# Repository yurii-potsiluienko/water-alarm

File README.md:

# Water Alarm

## Overview

This project was created to learn the fundamentals of PCB design using KiCad, develop mechanical CAD skills in FreeCAD by designing a 3D-printed enclosure, and build a practical, functional device.

The project was inspired by the [KiCad course by DigiKey on YouTube](https://www.youtube.com/watch?v=0WCi1rhueH4&list=PLEBQazB0HUyQ5YJSdCBb79orXaR3Uk5vm), with some modifications to the original circuit.

## Components

- [Buzzer](https://www.digikey.ca/en/products/detail/pui-audio-inc/AI-3035-TT-12V-R/9083403)
- [MOSFET](https://www.digikey.ca/en/products/detail/diotec-semiconductor/2N7000/13164314)
- [Screw terminal](https://www.digikey.ca/en/products/detail/adam-tech/EBAA-02-C/13586872)
- [LED](https://www.digikey.ca/en/products/detail/liteon/LTL-4234/200373)
- [10 MΩ resistor](https://www.digikey.ca/en/products/detail/stackpole-electronics-inc/CF18JT10M0/1741568)
- [6.8 kΩ resistor](https://www.digikey.ca/en/products/detail/stackpole-electronics-inc/CF18JT6K80/1741748)
- [1 nF capacitor](https://www.digikey.ca/en/products/detail/vishay-beyschlag-draloric-bc-components/K102K10X7RH5UL2/2820341)
- [Tactile switch](https://www.digikey.ca/en/products/detail/te-connectivity-alcoswitch-switches/1825910-6/1632536)
- [9 V battery](https://www.digikey.ca/en/products/detail/panasonic-energy/6LF22XWA-B/5067196)
- [Heat-set inserts](https://www.digikey.ca/en/products/detail/adafruit-industries-llc/4255/10244656)
- [M3 screws](https://www.digikey.ca/en/products/detail/w%C3%BCrth-elektronik/97790603111/10056387)

## Tools Used

- KiCad (schematic capture and PCB layout)
- FreeCAD (enclosure design)
- GitHub (version control and documentation)

## What I Learned

- Creating schematics in KiCad
- PCB component placement
- Trace routing and board layout
- Designing and 3D-printing an enclosure to fit a custom PCB

## Images

### Schematic

### PCB Layout

### 3D PCB View

### Enclosure

### Assembled PCB

### Assembled Device

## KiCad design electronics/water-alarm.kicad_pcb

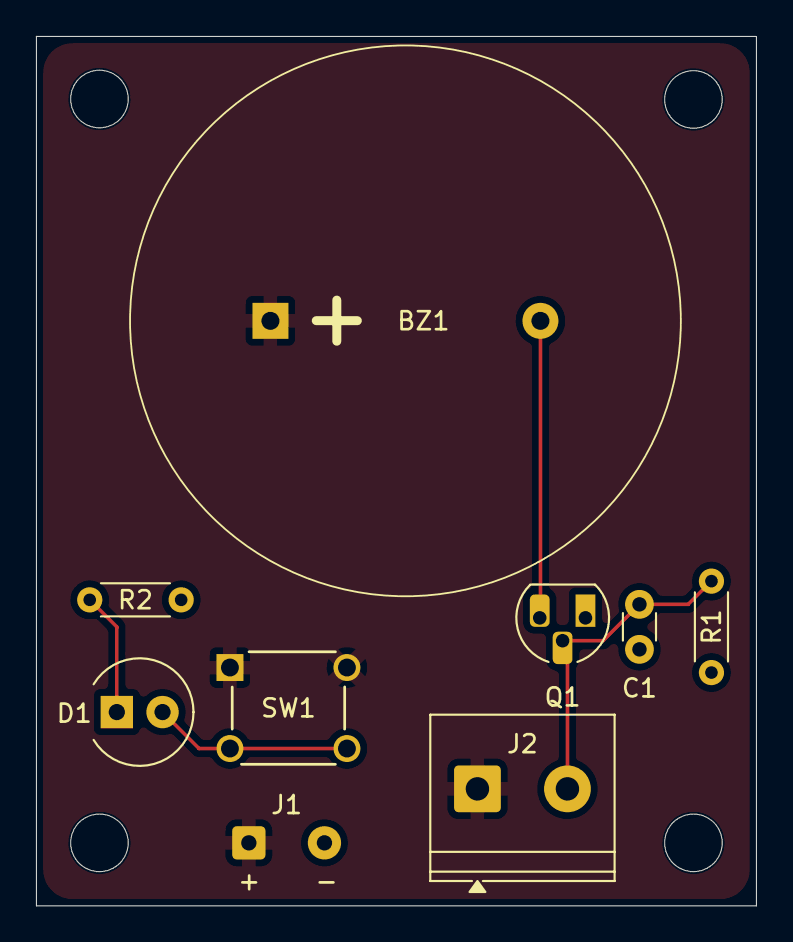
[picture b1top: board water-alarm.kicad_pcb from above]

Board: 2 copper layers, 40.0 x 48.3 mm, 9 parts (0 on the bottom side), 6 nets.

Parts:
BZ1: Buzzer; Buzzer_D30mm_H20mm_P15mm_668-1652-ND_AI-3035-TT-12V-R
C1: 1nF; C_Disc_D3.0mm_W1.6mm_P2.50mm
D1: LED_Small_Filled; LED_D5.0mm
J1: Conn_01x02_Socket; SolderWire-0.25sqmm_1x02_P4.2mm_D0.65mm_OD1.7mm
J2: Screw_Terminal_01x02; TerminalBlock_Phoenix_PT-1,5-2-5.0-H_1x02_P5.00mm_Horizontal
Q1: 2N7000; TO-92_HandSolder
R1: 10M; R_Axial_DIN0204_L3.6mm_D1.6mm_P5.08mm_Horizontal
R2: 6.8K; R_Axial_DIN0204_L3.6mm_D1.6mm_P5.08mm_Horizontal
SW1: 1825910-6 pushbutton switch

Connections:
/Gate: C1.1, J2.2, Q1.2 (G), R1.1
GND: C1.2, J1.2, Q1.1 (S), R1.2, R2.2
unnamed: BZ1.2 (-), Q1.3 (D)
unnamed: D1.2 (A), SW1.3, SW1.4
unnamed: D1.1 (K), R2.1
VCC: BZ1.1 (+), J1.1, J2.1, SW1.1, SW1.2
